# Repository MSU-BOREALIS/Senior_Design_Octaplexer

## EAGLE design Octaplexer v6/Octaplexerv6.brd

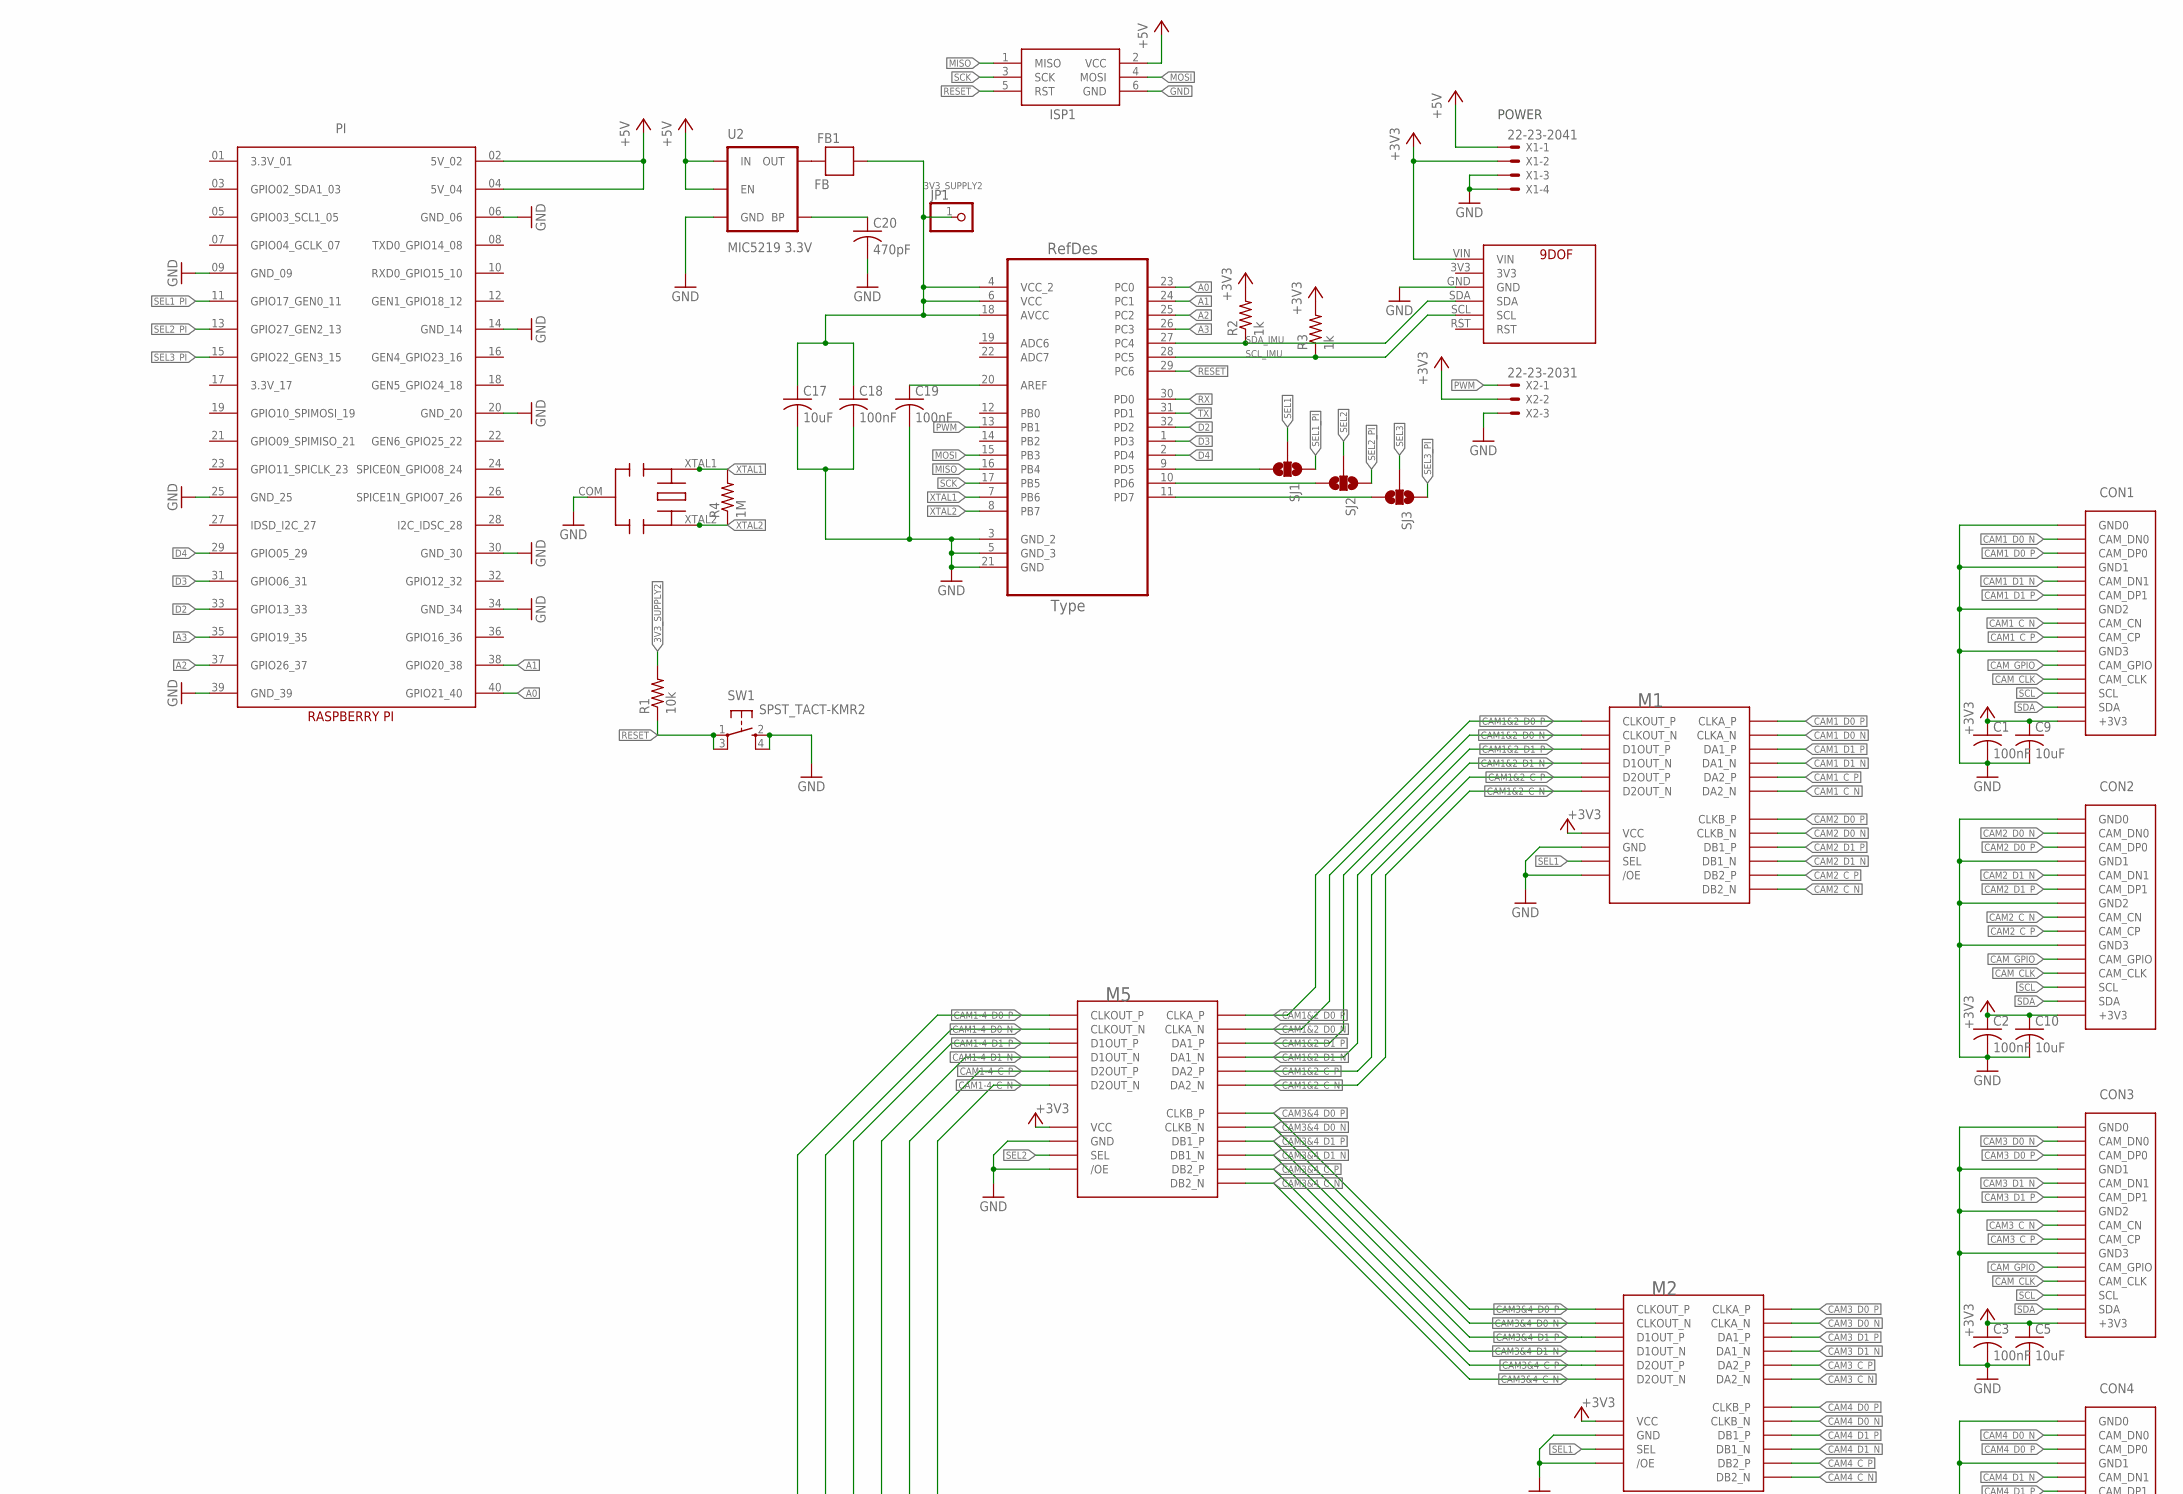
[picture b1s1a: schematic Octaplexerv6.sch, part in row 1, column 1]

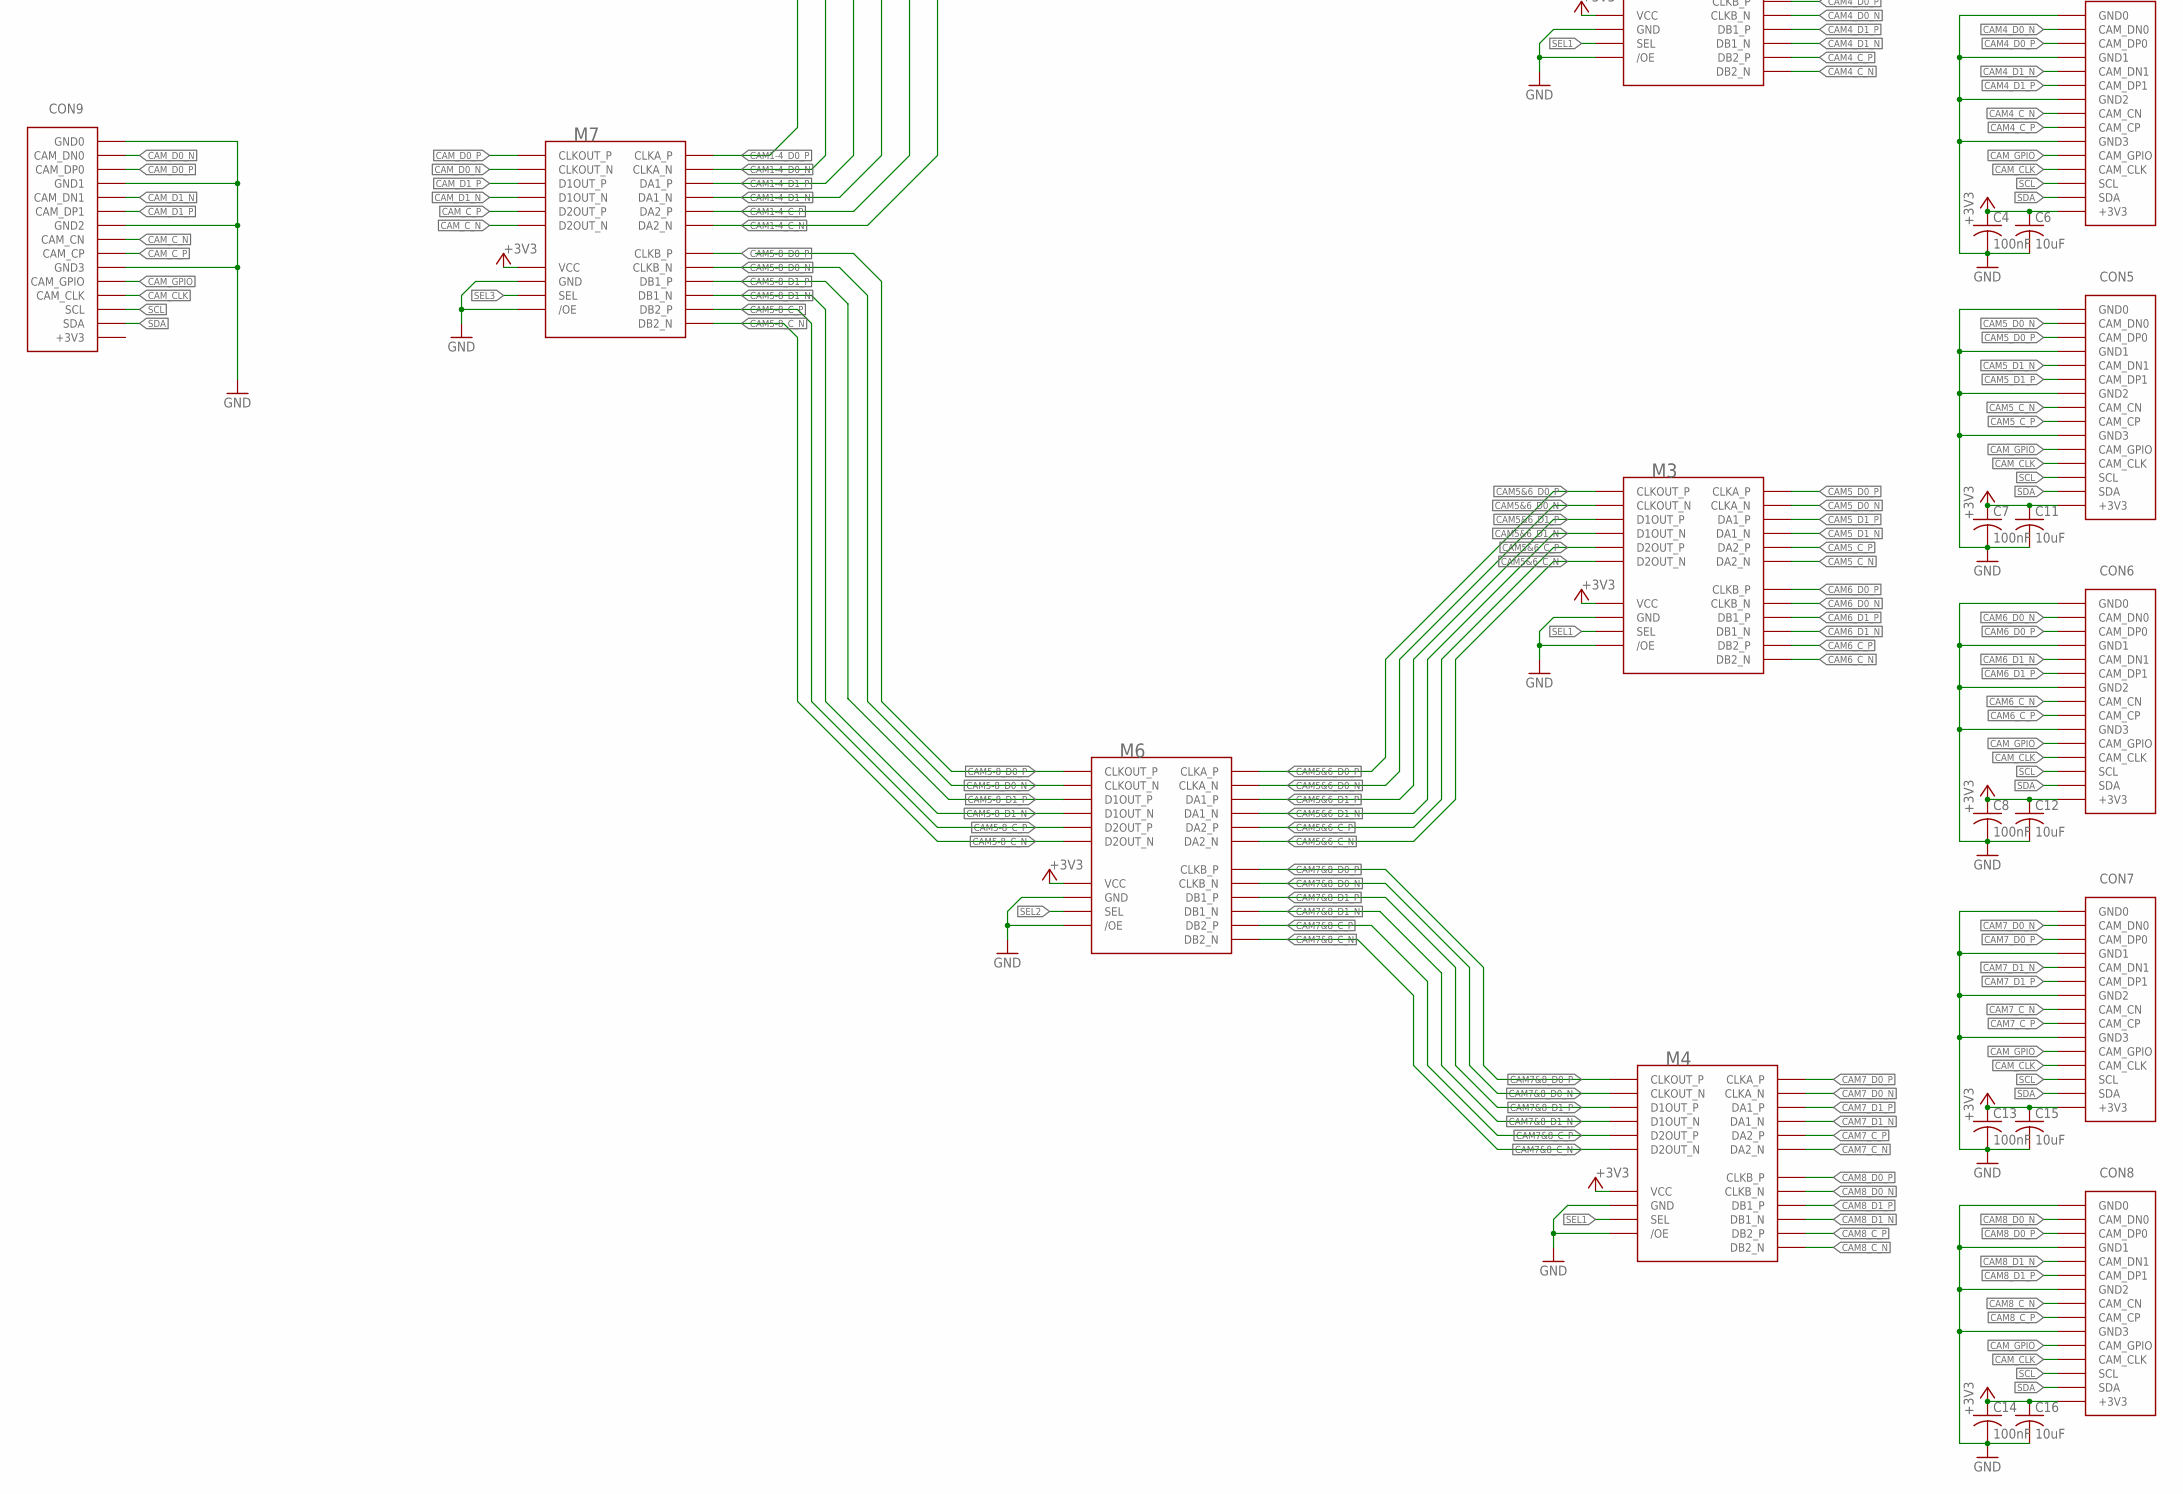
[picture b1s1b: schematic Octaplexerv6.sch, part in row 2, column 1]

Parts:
328P: ATMEGA328P-AU; QFP80P900X900X120-32N
C1, C2, C3, C4, C7, C8, C13, C14, C18, C19: 100nF; C0603
C5, C6, C9, C10, C11, C12, C15, C16, C17: 10uF; C0603
C20: 470pF; C0603
CON1, CON2, CON3, CON4, CON5, CON6, CON7, CON8, CON9: SLW15S-1C7LF; SLW15R-1C7LF
FB1: FB; 0603
ISP1: AVRISP-6; AVRISP
JP1: PINHD-1X1; 1X01
M1, M2, M3, M4, M5, M6, M7: FSA642
PI: RASPBERRYPI_SHIELD
R1: 10k; R0603
R2, R3: 1k; R0603
R4: 1M; R0603
SJ1, SJ2, SJ3: SOLDERJUMPER_2WAYPASTE2&3; SJ_3_PASTE2&3
SW1: SPST_TACT-KMR2; KMR2
U2: MIC5219 3.3V; SOT23-5
U$1: RESONATOR-PRQC; PRQC
U$2: 9DOF-BNO055; 9DOF_FLAT
X1: 22-23-2041
X2: 22-23-2031

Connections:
3V3_SUPPLY2: 328P.4 (VCC_2), 328P.6 (VCC), 328P.18 (AVCC), C17.1, C18.1, FB1.1, JP1.1, R1.2
+3V3: C1.1, C2.1, C3.1, C4.1, C5.1, C6.1, C7.1, C8.1, C9.1, C10.1, C11.1, C12.1, C13.1, C14.1, C15.1, C16.1, CON1.3.3V (+3V3), CON2.3.3V (+3V3), CON3.3.3V (+3V3), CON4.3.3V (+3V3), CON5.3.3V (+3V3), CON6.3.3V (+3V3), CON7.3.3V (+3V3), CON8.3.3V (+3V3), M1.VCC, M2.VCC, M3.VCC, M4.VCC, M5.VCC, M6.VCC, M7.VCC, R2.2, R3.2, U$2.VIN, X1.2, X2.2
+5V: ISP1.2 (VCC), PI.02 (5V_02), PI.04 (5V_04), U2.1 (IN), U2.3 (EN), X1.1
A0: 328P.23 (PC0), PI.40 (GPIO21_40)
A1: 328P.24 (PC1), PI.38 (GPIO20_38)
A2: 328P.25 (PC2), PI.37 (GPIO26_37)
A3: 328P.26 (PC3), PI.35 (GPIO19_35)
CAM1&2_C_N: M1.D2N (D2OUT_N), M5.DA2N (DA2_N)
CAM1&2_C_P: M1.D2P (D2OUT_P), M5.DA2P (DA2_P)
CAM1&2_D0_N: M1.CLKN (CLKOUT_N), M5.CLKAN (CLKA_N)
CAM1&2_D0_P: M1.CLKP (CLKOUT_P), M5.CLKAP (CLKA_P)
CAM1&2_D1_N: M1.D1N (D1OUT_N), M5.DA1N (DA1_N)
CAM1&2_D1_P: M1.D1P (D1OUT_P), M5.DA1P (DA1_P)
CAM1-4_C_N: M5.D2N (D2OUT_N), M7.DA2N (DA2_N)
CAM1-4_C_P: M5.D2P (D2OUT_P), M7.DA2P (DA2_P)
CAM1-4_D0_N: M5.CLKN (CLKOUT_N), M7.CLKAN (CLKA_N)
CAM1-4_D0_P: M5.CLKP (CLKOUT_P), M7.CLKAP (CLKA_P)
CAM1-4_D1_N: M5.D1N (D1OUT_N), M7.DA1N (DA1_N)
CAM1-4_D1_P: M5.D1P (D1OUT_P), M7.DA1P (DA1_P)
CAM1_C_N: CON1.CAM_C_N (CAM_CN), M1.DA2N (DA2_N)
CAM1_C_P: CON1.CAM_C_P (CAM_CP), M1.DA2P (DA2_P)
CAM1_D0_N: CON1.CAM_D0_N (CAM_DN0), M1.CLKAN (CLKA_N)
CAM1_D0_P: CON1.CAM_D0_P (CAM_DP0), M1.CLKAP (CLKA_P)
CAM1_D1_N: CON1.CAM_D1_N (CAM_DN1), M1.DA1N (DA1_N)
CAM1_D1_P: CON1.CAM_D1_P (CAM_DP1), M1.DA1P (DA1_P)
CAM2_C_N: CON2.CAM_C_N (CAM_CN), M1.DB2N (DB2_N)
CAM2_C_P: CON2.CAM_C_P (CAM_CP), M1.DB2P (DB2_P)
CAM2_D0_N: CON2.CAM_D0_N (CAM_DN0), M1.CLKBN (CLKB_N)
CAM2_D0_P: CON2.CAM_D0_P (CAM_DP0), M1.CLKBP (CLKB_P)
CAM2_D1_N: CON2.CAM_D1_N (CAM_DN1), M1.DB1N (DB1_N)
CAM2_D1_P: CON2.CAM_D1_P (CAM_DP1), M1.DB1P (DB1_P)
CAM3&4_C_N: M2.D2N (D2OUT_N), M5.DB2N (DB2_N)
CAM3&4_C_P: M2.D2P (D2OUT_P), M5.DB2P (DB2_P)
CAM3&4_D0_N: M2.CLKN (CLKOUT_N), M5.CLKBN (CLKB_N)
CAM3&4_D0_P: M2.CLKP (CLKOUT_P), M5.CLKBP (CLKB_P)
CAM3&4_D1_N: M2.D1N (D1OUT_N), M5.DB1N (DB1_N)
CAM3&4_D1_P: M2.D1P (D1OUT_P), M5.DB1P (DB1_P)
CAM3_C_N: CON3.CAM_C_N (CAM_CN), M2.DA2N (DA2_N)
CAM3_C_P: CON3.CAM_C_P (CAM_CP), M2.DA2P (DA2_P)
CAM3_D0_N: CON3.CAM_D0_N (CAM_DN0), M2.CLKAN (CLKA_N)
CAM3_D0_P: CON3.CAM_D0_P (CAM_DP0), M2.CLKAP (CLKA_P)
CAM3_D1_N: CON3.CAM_D1_N (CAM_DN1), M2.DA1N (DA1_N)
CAM3_D1_P: CON3.CAM_D1_P (CAM_DP1), M2.DA1P (DA1_P)
CAM4_C_N: CON4.CAM_C_N (CAM_CN), M2.DB2N (DB2_N)
CAM4_C_P: CON4.CAM_C_P (CAM_CP), M2.DB2P (DB2_P)
CAM4_D0_N: CON4.CAM_D0_N (CAM_DN0), M2.CLKBN (CLKB_N)
CAM4_D0_P: CON4.CAM_D0_P (CAM_DP0), M2.CLKBP (CLKB_P)
CAM4_D1_N: CON4.CAM_D1_N (CAM_DN1), M2.DB1N (DB1_N)
CAM4_D1_P: CON4.CAM_D1_P (CAM_DP1), M2.DB1P (DB1_P)
CAM5&6_C_N: M3.D2N (D2OUT_N), M6.DA2N (DA2_N)
CAM5&6_C_P: M3.D2P (D2OUT_P), M6.DA2P (DA2_P)
CAM5&6_D0_N: M3.CLKN (CLKOUT_N), M6.CLKAN (CLKA_N)
CAM5&6_D0_P: M3.CLKP (CLKOUT_P), M6.CLKAP (CLKA_P)
CAM5&6_D1_N: M3.D1N (D1OUT_N), M6.DA1N (DA1_N)
CAM5&6_D1_P: M3.D1P (D1OUT_P), M6.DA1P (DA1_P)
CAM5-8_C_N: M6.D2N (D2OUT_N), M7.DB2N (DB2_N)
CAM5-8_C_P: M6.D2P (D2OUT_P), M7.DB2P (DB2_P)
CAM5-8_D0_N: M6.CLKN (CLKOUT_N), M7.CLKBN (CLKB_N)
CAM5-8_D0_P: M6.CLKP (CLKOUT_P), M7.CLKBP (CLKB_P)
CAM5-8_D1_N: M6.D1N (D1OUT_N), M7.DB1N (DB1_N)
CAM5-8_D1_P: M6.D1P (D1OUT_P), M7.DB1P (DB1_P)
CAM5_C_N: CON5.CAM_C_N (CAM_CN), M3.DA2N (DA2_N)
CAM5_C_P: CON5.CAM_C_P (CAM_CP), M3.DA2P (DA2_P)
CAM5_D0_N: CON5.CAM_D0_N (CAM_DN0), M3.CLKAN (CLKA_N)
CAM5_D0_P: CON5.CAM_D0_P (CAM_DP0), M3.CLKAP (CLKA_P)
CAM5_D1_N: CON5.CAM_D1_N (CAM_DN1), M3.DA1N (DA1_N)
CAM5_D1_P: CON5.CAM_D1_P (CAM_DP1), M3.DA1P (DA1_P)
CAM6_C_N: CON6.CAM_C_N (CAM_CN), M3.DB2N (DB2_N)
CAM6_C_P: CON6.CAM_C_P (CAM_CP), M3.DB2P (DB2_P)
CAM6_D0_N: CON6.CAM_D0_N (CAM_DN0), M3.CLKBN (CLKB_N)
CAM6_D0_P: CON6.CAM_D0_P (CAM_DP0), M3.CLKBP (CLKB_P)
CAM6_D1_N: CON6.CAM_D1_N (CAM_DN1), M3.DB1N (DB1_N)
CAM6_D1_P: CON6.CAM_D1_P (CAM_DP1), M3.DB1P (DB1_P)
CAM7&8_C_N: M4.D2N (D2OUT_N), M6.DB2N (DB2_N)
CAM7&8_C_P: M4.D2P (D2OUT_P), M6.DB2P (DB2_P)
CAM7&8_D0_N: M4.CLKN (CLKOUT_N), M6.CLKBN (CLKB_N)
CAM7&8_D0_P: M4.CLKP (CLKOUT_P), M6.CLKBP (CLKB_P)
CAM7&8_D1_N: M4.D1N (D1OUT_N), M6.DB1N (DB1_N)
CAM7&8_D1_P: M4.D1P (D1OUT_P), M6.DB1P (DB1_P)
CAM7_C_N: CON7.CAM_C_N (CAM_CN), M4.DA2N (DA2_N)
CAM7_C_P: CON7.CAM_C_P (CAM_CP), M4.DA2P (DA2_P)
CAM7_D0_N: CON7.CAM_D0_N (CAM_DN0), M4.CLKAN (CLKA_N)
CAM7_D0_P: CON7.CAM_D0_P (CAM_DP0), M4.CLKAP (CLKA_P)
CAM7_D1_N: CON7.CAM_D1_N (CAM_DN1), M4.DA1N (DA1_N)
CAM7_D1_P: CON7.CAM_D1_P (CAM_DP1), M4.DA1P (DA1_P)
CAM8_C_N: CON8.CAM_C_N (CAM_CN), M4.DB2N (DB2_N)
CAM8_C_P: CON8.CAM_C_P (CAM_CP), M4.DB2P (DB2_P)
CAM8_D0_N: CON8.CAM_D0_N (CAM_DN0), M4.CLKBN (CLKB_N)
CAM8_D0_P: CON8.CAM_D0_P (CAM_DP0), M4.CLKBP (CLKB_P)
CAM8_D1_N: CON8.CAM_D1_N (CAM_DN1), M4.DB1N (DB1_N)
CAM8_D1_P: CON8.CAM_D1_P (CAM_DP1), M4.DB1P (DB1_P)
CAM_CLK: CON1.CAM_CLK, CON2.CAM_CLK, CON3.CAM_CLK, CON4.CAM_CLK, CON5.CAM_CLK, CON6.CAM_CLK, CON7.CAM_CLK, CON8.CAM_CLK, CON9.CAM_CLK
CAM_C_N: CON9.CAM_C_N (CAM_CN), M7.D2N (D2OUT_N)
CAM_C_P: CON9.CAM_C_P (CAM_CP), M7.D2P (D2OUT_P)
CAM_D0_N: CON9.CAM_D0_N (CAM_DN0), M7.CLKN (CLKOUT_N)
CAM_D0_P: CON9.CAM_D0_P (CAM_DP0), M7.CLKP (CLKOUT_P)
CAM_D1_N: CON9.CAM_D1_N (CAM_DN1), M7.D1N (D1OUT_N)
CAM_D1_P: CON9.CAM_D1_P (CAM_DP1), M7.D1P (D1OUT_P)
CAM_GPIO: CON1.CAM_GPIO, CON2.CAM_GPIO, CON3.CAM_GPIO, CON4.CAM_GPIO, CON5.CAM_GPIO, CON6.CAM_GPIO, CON7.CAM_GPIO, CON8.CAM_GPIO, CON9.CAM_GPIO
D2: 328P.32 (PD2), PI.33 (GPIO13_33)
D3: 328P.1 (PD3), PI.31 (GPIO06_31)
D4: 328P.2 (PD4), PI.29 (GPIO05_29)
GND: 328P.3 (GND_2), 328P.5 (GND_3), 328P.21 (GND), C1.2, C2.2, C3.2, C4.2, C5.2, C6.2, C7.2, C8.2, C9.2, C10.2, C11.2, C12.2, C13.2, C14.2, C15.2, C16.2, C17.2, C18.2, C19.2, C20.2, CON1.GND (GND0), CON1.GND1, CON1.GND2, CON1.GND3, CON2.GND (GND0), CON2.GND1, CON2.GND2, CON2.GND3, CON3.GND (GND0), CON3.GND1, CON3.GND2, CON3.GND3, CON4.GND (GND0), CON4.GND1, CON4.GND2, CON4.GND3, CON5.GND (GND0), CON5.GND1, CON5.GND2, CON5.GND3, CON6.GND (GND0), CON6.GND1, CON6.GND2, CON6.GND3, CON7.GND (GND0), CON7.GND1, CON7.GND2, CON7.GND3, CON8.GND (GND0), CON8.GND1, CON8.GND2, CON8.GND3, CON9.GND (GND0), CON9.GND1, CON9.GND2, CON9.GND3, ISP1.6 (GND), M1./OE, M1.GND, M2./OE, M2.GND, M3./OE, M3.GND, M4./OE, M4.GND, M5./OE, M5.GND, M6./OE, M6.GND, M7./OE, M7.GND, PI.06 (GND_06), PI.09 (GND_09), PI.14 (GND_14), PI.20 (GND_20), PI.25 (GND_25), PI.30 (GND_30), PI.34 (GND_34), PI.39 (GND_39), SW1.2 (S), SW1.4 (S1), U2.2 (GND), U$1.COM, U$2.GND, X1.3, X1.4, X2.3
MISO: 328P.16 (PB4), ISP1.1 (MISO)
MOSI: 328P.15 (PB3), ISP1.4 (MOSI)
unnamed: 328P.11 (PD7), SJ3.3
unnamed: 328P.20 (AREF), C19.1
unnamed: 328P.10 (PD6), SJ2.3
unnamed: 328P.9 (PD5), SJ1.3
unnamed: FB1.2, U2.5 (OUT)
unnamed: C20.1, U2.4 (BP)
PWM: 328P.13 (PB1), X2.1
RESET: 328P.29 (PC6), ISP1.5 (RST), R1.1, SW1.1, SW1.3 (P1)
RX: 328P.30 (PD0)
SCK: 328P.17 (PB5), ISP1.3 (SCK)
SCL: CON1.SCL, CON2.SCL, CON3.SCL, CON4.SCL, CON5.SCL, CON6.SCL, CON7.SCL, CON8.SCL, CON9.SCL
SCL_IMU: 328P.28 (PC5), R3.1, U$2.SCL
SDA: CON1.SDA, CON2.SDA, CON3.SDA, CON4.SDA, CON5.SDA, CON6.SDA, CON7.SDA, CON8.SDA, CON9.SDA
SDA_IMU: 328P.27 (PC4), R2.1, U$2.SDA
SEL1: M1.SEL, M2.SEL, M3.SEL, M4.SEL, SJ1.2
SEL1_PI: PI.11 (GPIO17_GEN0_11), SJ1.1
SEL2: M5.SEL, M6.SEL, SJ2.2
SEL2_PI: PI.13 (GPIO27_GEN2_13), SJ2.1
SEL3: M7.SEL, SJ3.2
SEL3_PI: PI.15 (GPIO22_GEN3_15), SJ3.1
TX: 328P.31 (PD1)
XTAL1: 328P.7 (PB6), R4.2, U$1.XTAL1
XTAL2: 328P.8 (PB7), R4.1, U$1.XTAL2

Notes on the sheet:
POWER

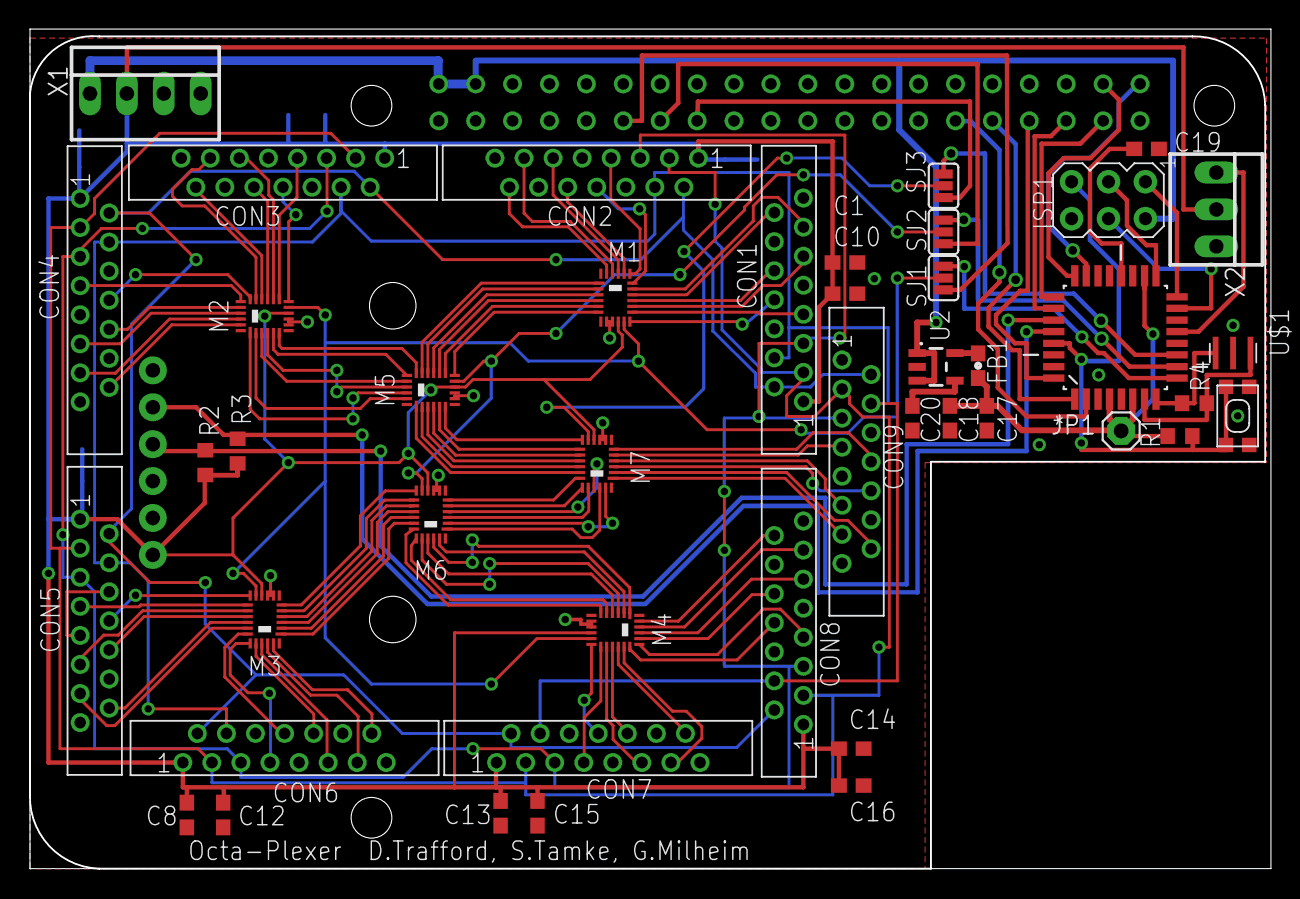
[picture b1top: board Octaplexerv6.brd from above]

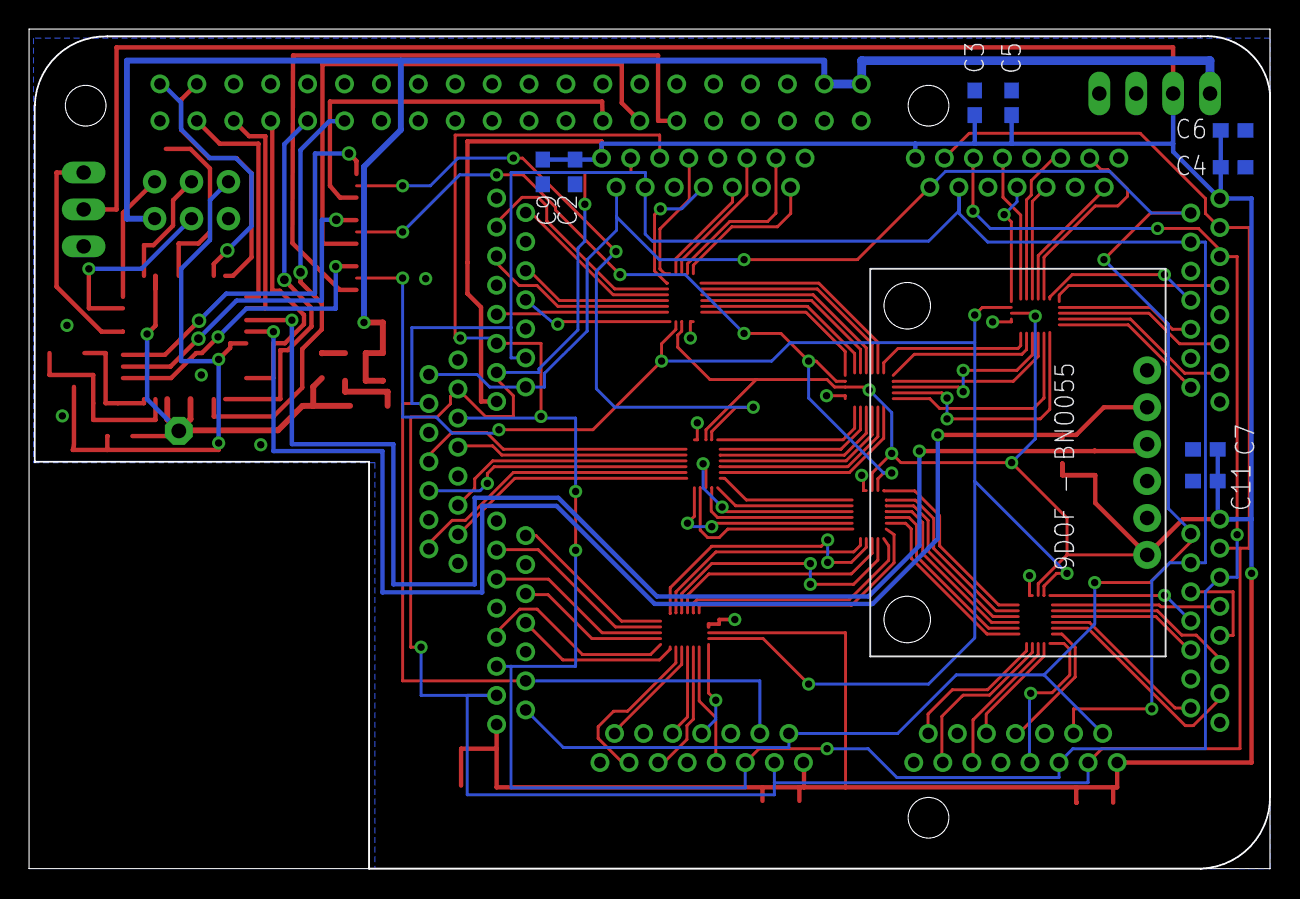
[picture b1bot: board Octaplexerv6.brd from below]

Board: 2 copper layers, 85.4 x 57.8 mm, 54 parts (9 on the bottom side), 126 nets.

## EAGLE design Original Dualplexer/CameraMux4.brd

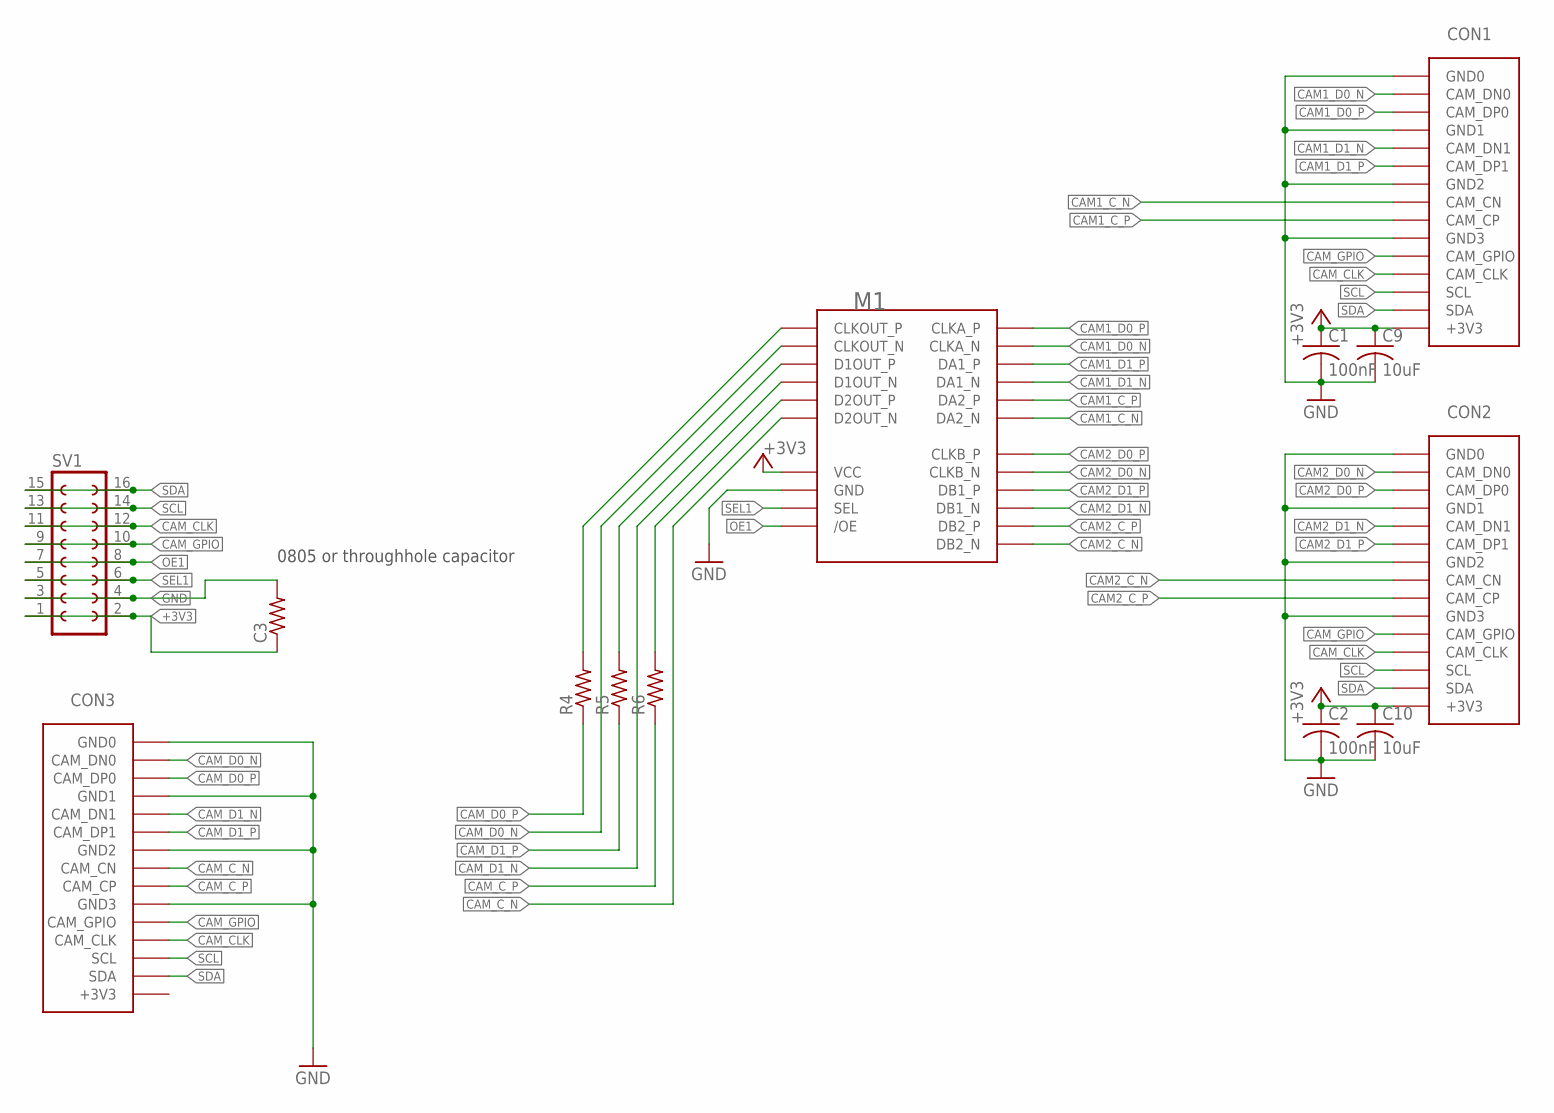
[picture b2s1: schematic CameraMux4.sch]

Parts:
C1, C2: 100nF; C0603
C3: R-US_FLIPFLOP; 0805-THM
C9, C10: 10uF; C0603
CON1, CON2, CON3: XF3M(1)-1515-1B
M1: FSA642
R4, R5, R6: R-US_R0603; R0603
SV1: FE08-2

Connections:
+3V3: C1.1, C2.1, C3.1, C9.1, C10.1, CON1.3V3 (+3V3), CON2.3V3 (+3V3), M1.VCC, SV1.1, SV1.2
CAM1_C_N: CON1.CAM_CN, M1.DA2N (DA2_N)
CAM1_C_P: CON1.CAM_CP, M1.DA2P (DA2_P)
CAM1_D0_N: CON1.CAM_DN0, M1.CLKAN (CLKA_N)
CAM1_D0_P: CON1.CAM_DP0, M1.CLKAP (CLKA_P)
CAM1_D1_N: CON1.CAM_DN1, M1.DA1N (DA1_N)
CAM1_D1_P: CON1.CAM_DP1, M1.DA1P (DA1_P)
CAM2_C_N: CON2.CAM_CN, M1.DB2N (DB2_N)
CAM2_C_P: CON2.CAM_CP, M1.DB2P (DB2_P)
CAM2_D0_N: CON2.CAM_DN0, M1.CLKBN (CLKB_N)
CAM2_D0_P: CON2.CAM_DP0, M1.CLKBP (CLKB_P)
CAM2_D1_N: CON2.CAM_DN1, M1.DB1N (DB1_N)
CAM2_D1_P: CON2.CAM_DP1, M1.DB1P (DB1_P)
CAM_CLK: CON1.CAM_CLK, CON2.CAM_CLK, CON3.CAM_CLK, SV1.11, SV1.12
CAM_C_N: CON3.CAM_CN, M1.D2N (D2OUT_N)
CAM_C_P: CON3.CAM_CP, R6.1
CAM_D0_N: CON3.CAM_DN0, M1.CLKN (CLKOUT_N)
CAM_D0_P: CON3.CAM_DP0, R4.1
CAM_D1_N: CON3.CAM_DN1, M1.D1N (D1OUT_N)
CAM_D1_P: CON3.CAM_DP1, R5.1
CAM_GPIO: CON1.CAM_GPIO, CON2.CAM_GPIO, CON3.CAM_GPIO, SV1.9, SV1.10
GND: C1.2, C2.2, C3.2, C9.2, C10.2, CON1.GND0, CON1.GND1, CON1.GND2, CON1.GND3, CON2.GND0, CON2.GND1, CON2.GND2, CON2.GND3, CON3.GND0, CON3.GND1, CON3.GND2, CON3.GND3, M1.GND, SV1.3, SV1.4
unnamed: M1.D2P (D2OUT_P), R6.2
unnamed: M1.D1P (D1OUT_P), R5.2
unnamed: M1.CLKP (CLKOUT_P), R4.2
OE1: M1./OE, SV1.7, SV1.8
SCL: CON1.SCL, CON2.SCL, CON3.SCL, SV1.13, SV1.14
SDA: CON1.SDA, CON2.SDA, CON3.SDA, SV1.15, SV1.16
SEL1: M1.SEL, SV1.5, SV1.6

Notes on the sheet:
0805 or throughhole capacitor

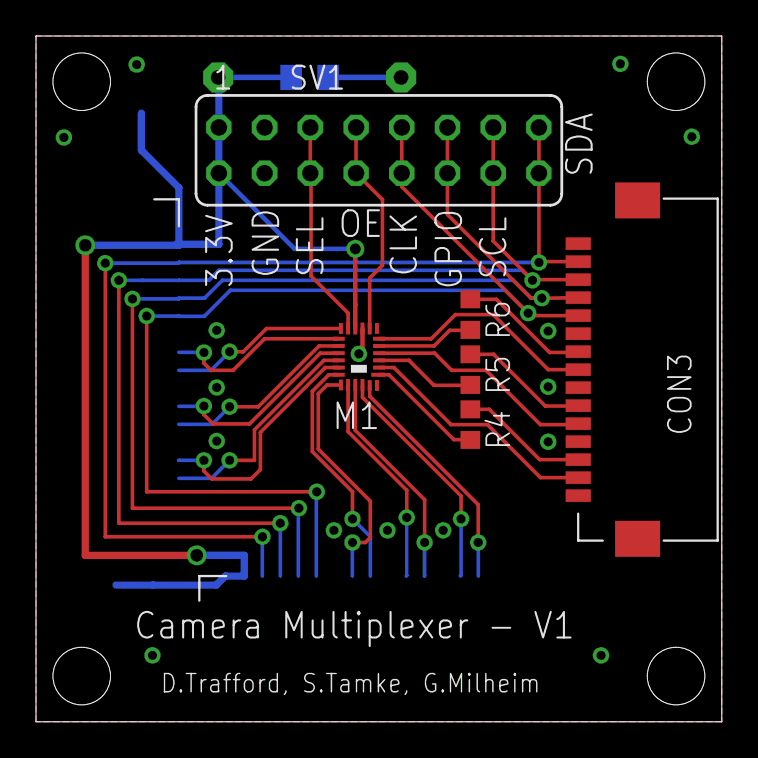
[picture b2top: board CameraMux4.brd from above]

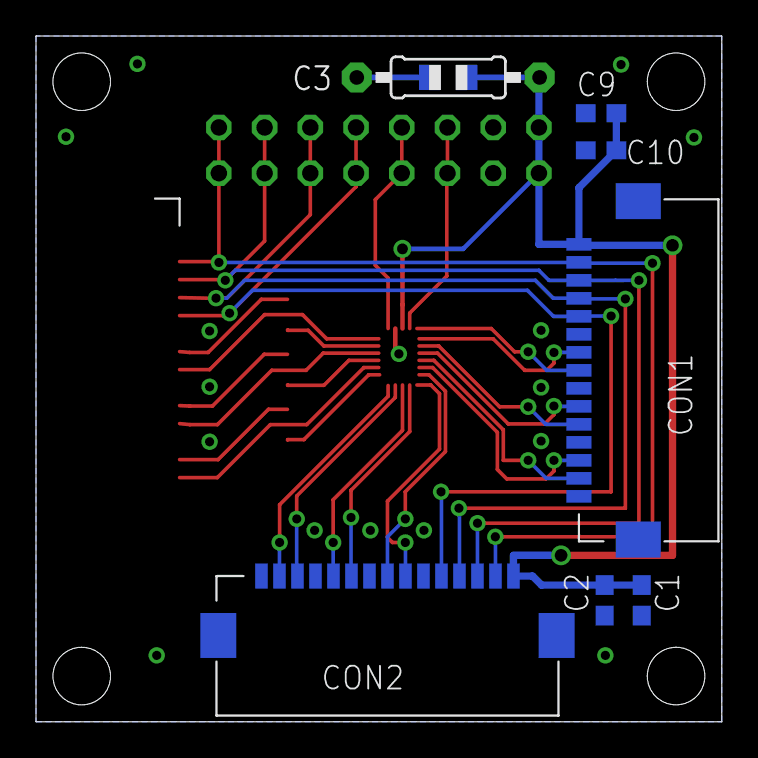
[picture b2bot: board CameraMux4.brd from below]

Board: 2 copper layers, 38.1 x 38.1 mm, 13 parts (7 on the bottom side), 29 nets.

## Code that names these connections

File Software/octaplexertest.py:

import os
import RPi.GPIO as GPIO
import time

sel1 = 17
sel2 = 27 
sel3 = 22
GPIO.setmode(GPIO.BCM)
GPIO.setup(sel1,GPIO.OUT)
GPIO.setup(sel2,GPIO.OUT)
GPIO.setup(sel3,GPIO.OUT)

def cam1():
    GPIO.output(sel1,GPIO.LOW)
    GPIO.output(sel2,GPIO.LOW)
    GPIO.output(sel3,GPIO.LOW)
def cam2():
    GPIO.output(sel1,GPIO.HIGH)
    GPIO.output(sel2,GPIO.LOW)
    GPIO.output(sel3,GPIO.LOW)
def cam3():
    GPIO.output(sel1,GPIO.LOW)
    GPIO.output(sel2,GPIO.HIGH)
    GPIO.output(sel3,GPIO.LOW)
def cam4():
    GPIO.output(sel1,GPIO.HIGH)
    GPIO.output(sel2,GPIO.HIGH)
    GPIO.output(sel3,GPIO.LOW)
def cam5():
    GPIO.output(sel1,GPIO.LOW)
    GPIO.output(sel2,GPIO.LOW)
    GPIO.output(sel3,GPIO.HIGH)
def cam6():
    GPIO.output(sel1,GPIO.HIGH)
    GPIO.output(sel2,GPIO.LOW)
    GPIO.output(sel3,GPIO.HIGH)
def cam7():
    GPIO.output(sel1,GPIO.LOW)
    GPIO.output(sel2,GPIO.HIGH)
    GPIO.output(sel3,GPIO.HIGH)
def cam8():
    GPIO.output(sel1,GPIO.HIGH)
    GPIO.output(sel2,GPIO.HIGH)
    GPIO.output(sel3,GPIO.HIGH)

while(1):
    cam1()
    time.sleep(3)
    cam2()
    time.sleep(3)
    cam3()
    time.sleep(3)
    cam4()
    time.sleep(3)
    cam5()
    time.sleep(3)
    cam6()
    time.sleep(3)
    cam7()
    time.sleep(3)
    cam8()
    time.sleep(3)

GPIO.cleanup()
    

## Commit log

2016-07-13 Senior Design Project 2015-2016 for Montana State Uni (MSU)
2016-07-13 added a readme for some explanation
2016-08-19 Raspberry Pi side code
    This is the code to tell the AtMega328 what to do.
2017-03-24 added hex and actual file
2017-04-12 added shell script to streamline process for new processors
2017-05-19 found the missing star child

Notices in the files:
parts and their libraries:
SparkFun-PowerIC: Licensing: Creative Commons ShareAlike 4.0 International - https://creativecommons.org/licenses/by-sa/4.0
